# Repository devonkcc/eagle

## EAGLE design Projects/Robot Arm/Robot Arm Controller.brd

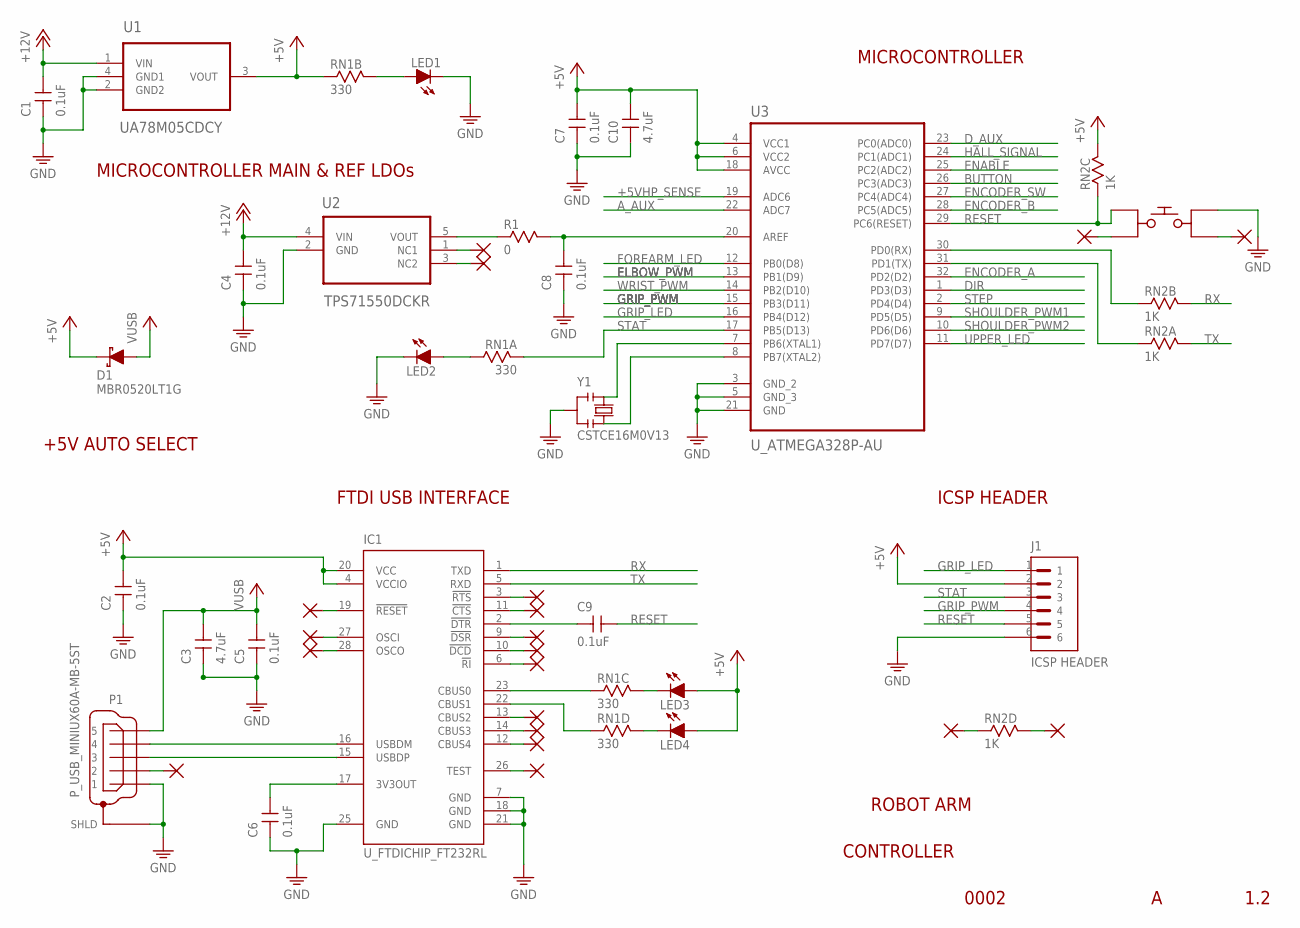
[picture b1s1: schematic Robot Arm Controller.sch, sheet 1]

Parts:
C1, C2, C4, C5, C6, C7, C8, C9: 0.1uF; C0805
C3, C10: 4.7uF; C0805
D1: MBR0520LT1G
IC1: U_FTDICHIP_FT232RL; SSOP28
J1: ICSP HEADER; RECTANGULAR_HEADER_2X3
LED1, LED2, LED3, LED4: D_LEDSML0805; SML0805
P1: P_USB_MINIUX60A-MB-5ST; UX60A-MB-5ST
R1: 0; R0805
RN1: 330; EXBV8V
RN2: 1K; EXBV8V
S1: S_BUTTON_TACTILE_PTS645; PTS645-SMD
U1: UA78M05CDCY; SOT230P700X180-4N
U2: TPS71550DCKR; SOT65P210X110-5N
U3: U_ATMEGA328P-AU; QFP80P900X900X120-32N
Y1: CSTCE16M0V13; CSTCE_V13L

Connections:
+5V: C2.1, C7.1, C10.1, D1.C, IC1.4 (VCCIO), IC1.20 (VCC), J1.2, LED3.A, LED4.A, RN1.2A (1), RN2.3B (2), U1.3 (VOUT), U3.4 (VCC1), U3.6 (VCC2), U3.18 (AVCC); also elsewhere on the board
+5VHP_SENSE: U3.19 (ADC6); also elsewhere on the board
+12V: C1.1, C4.1, U1.1 (VIN), U2.4 (VIN); also elsewhere on the board
A_AUX: U3.22 (ADC7); also elsewhere on the board
BUTTON: U3.26 (PC3(ADC3)); also elsewhere on the board
DIR: U3.1 (PD3(D3)); also elsewhere on the board
D_AUX: U3.23 (PC0(ADC0)); also elsewhere on the board
ELBOW_PWM: U3.13 (PB1(D9)); also elsewhere on the board
ENABLE: U3.25 (PC2(ADC2)); also elsewhere on the board
ENCODER_A: U3.32 (PD2(D2)); also elsewhere on the board
ENCODER_B: U3.28 (PC5(ADC5)); also elsewhere on the board
ENCODER_SW: U3.27 (PC4(ADC4)); also elsewhere on the board
FOREARM_LED: U3.12 (PB0(D8)); also elsewhere on the board
GND: C1.2, C2.2, C3.2, C4.2, C5.2, C6.2, C7.2, C8.2, C10.2, IC1.7 (GND), IC1.18 (GND), IC1.21 (GND), IC1.25 (GND), J1.6, LED1.C, LED2.C, P1.5 (1), P1.M1 (SHLD), P1.M2 (SHLD), P1.M3 (SHLD), P1.M4 (SHLD), S1.1, U1.2 (GND2), U1.4 (GND1), U2.2 (GND), U3.3 (GND_2), U3.5 (GND_3), U3.21 (GND), Y1.2; also elsewhere on the board
GRIP_LED: J1.1, U3.16 (PB4(D12)); also elsewhere on the board
GRIP_PWM: J1.4, U3.15 (PB3(D11)); also elsewhere on the board
HALL_SIGNAL: U3.24 (PC1(ADC1)); also elsewhere on the board
unnamed: LED2.A, RN1.1B (2)
unnamed: U3.8 (PB7(XTAL2)), Y1.3
unnamed: C8.1, R1.2, U3.20 (AREF)
unnamed: IC1.16 (USBDM), P1.2 (4)
unnamed: RN2.1A (1), U3.31 (PD1(TX))
unnamed: C6.1, IC1.17 (3V3OUT)
unnamed: U3.7 (PB6(XTAL1)), Y1.1
unnamed: LED1.A, RN1.2B (2)
unnamed: R1.1, U2.5 (VOUT)
unnamed: RN2.2A (1), U3.30 (PD0(RX))
unnamed: IC1.15 (USBDP), P1.3
unnamed: C9.2, IC1.2 (!DTR)
unnamed: IC1.23 (CBUS0), RN1.3A (1)
unnamed: IC1.22 (CBUS1), RN1.4A (1)
unnamed: LED3.C, RN1.3B (2)
unnamed: LED4.C, RN1.4B (2)
RESET: C9.1, J1.5, RN2.3A (1), S1.3, U3.29 (PC6(RESET))
RX: IC1.1 (TXD), RN2.2B (2)
SHOULDER_PWM1: U3.9 (PD5(D5)); also elsewhere on the board
SHOULDER_PWM2: U3.10 (PD6(D6)); also elsewhere on the board
STAT: J1.3, RN1.1A (1), U3.17 (PB5(D13))
STEP: U3.2 (PD4(D4)); also elsewhere on the board
TX: IC1.5 (RXD), RN2.1B (2)
UPPER_LED: U3.11 (PD7(D7)); also elsewhere on the board
VUSB: C3.1, C5.1, D1.A, P1.1 (5)
WRIST_PWM: U3.14 (PB2(D10)); also elsewhere on the board

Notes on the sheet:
1.2
ROBOT ARM
0002
CONTROLLER
FTDI USB INTERFACE
+5V AUTO SELECT
MICROCONTROLLER MAIN & REF LDOs
MICROCONTROLLER
ICSP HEADER

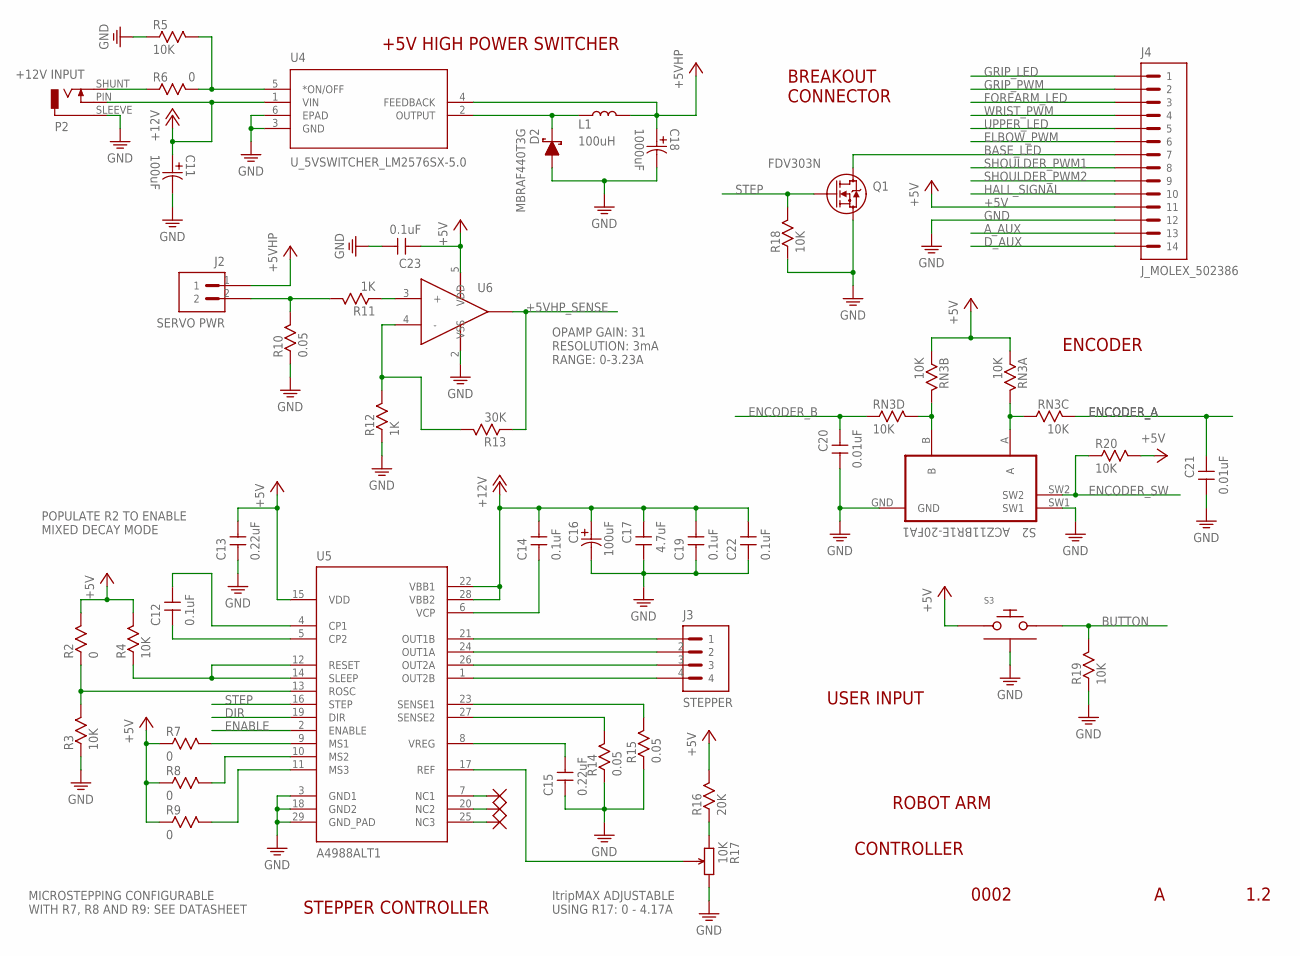
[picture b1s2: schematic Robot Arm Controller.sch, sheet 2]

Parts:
C11, C16: 100uF; NPCAP_PXG_E61
C12, C14, C19, C22, C23: 0.1uF; C0805
C13, C15: 0.22uF; C0805
C17: 4.7uF; C0805
C18: 1000uF; NPCAP_PXG_JA0
C20, C21: 0.01uF; C0805
D2: MBRAF440T3G
J2: SERVO PWR; SREW_TERMINAL_2_POS
J3: STEPPER; SREW_TERMINAL_4_POS
J4: J_MOLEX_502386; MOLEX_502386
L1: 100uH; PA4344.104NLT
P2: +12V INPUT; RASM722PX
Q1: FDV303N; SOT-23-3L
R2, R6, R7, R8, R9: 0; R0805
R3, R4, R5, R18, R19, R20: 10K; R0805
R10, R14, R15: 0.05; R1206
R11, R12: 1K; R0805
R13: 30K; R0805
R16: 20K; R0805
R17: 10K; PANASONIC_P2W_POT
RN3: 10K; EXBV8V
S2: ACZ11BR1E-20FA1; ACZ11BR1E-20FA1-20C
S3: S_BUTTON_TACTILE_KT11S1SA2M35LFG; C&K_SA2M_SA1M
U4: U_5VSWITCHER_LM2576SX-5.0; KTT5_6P22X6P86
U5: A4988ALT1; ALLEGRO_A4988
U6: U_OPAMP_MCP6001T-E/OT; SOT95P270X145-5N

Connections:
+5V: C13.1, C23.2, J4.P11 (11), R2.2, R4.2, R7.1, R8.1, R9.1, R16.2, R20.2, RN3.1A (1), RN3.2A (1), S3.1, U5.15 (VDD), U6.5 (VDD); also elsewhere on the board
+5VHP: C18.+, J2.1, L1.2, U4.4 (FEEDBACK)
+5VHP_SENSE: R13.1, U6.1 (VOUT); also elsewhere on the board
+12V: C11.+, C14.1, C16.+, C17.2, C19.1, C22.1, P2.PIN, U4.1 (VIN), U5.22 (VBB1), U5.28 (VBB2); also elsewhere on the board
A_AUX: J4.P13 (13); also elsewhere on the board
BASE_LED: J4.P7 (7), Q1.S (DRAIN)
BUTTON: R19.2, S3.2; also elsewhere on the board
DIR: U5.19 (DIR); also elsewhere on the board
D_AUX: J4.P14 (14); also elsewhere on the board
ELBOW_PWM: J4.P6 (6); also elsewhere on the board
ENABLE: U5.2 (ENABLE); also elsewhere on the board
ENCODER_A: C21.2, RN3.3A (1); also elsewhere on the board
ENCODER_B: C20.2, RN3.4A (1); also elsewhere on the board
ENCODER_SW: R20.1, S2.SW2; also elsewhere on the board
FOREARM_LED: J4.P3 (3); also elsewhere on the board
GND: C11.-, C13.2, C15.2, C16.-, C17.1, C18.-, C19.2, C20.1, C21.1, C22.2, C23.1, D2.A, J4.P12 (12), P2.SLEEVE, Q1.D (SOURCE), R3.1, R5.1, R10.1, R12.1, R14.1, R15.1, R17.3, R18.1, R19.1, S2.GND, S2.SW1, S3.FRONT (HOUSING), S3.SIDE1 (HOUSING), S3.SIDE2 (HOUSING), U4.3 (GND), U4.6 (EPAD), U5.3 (GND1), U5.18 (GND2), U5.29 (GND_PAD), U6.2 (VSS); also elsewhere on the board
GRIP_LED: J4.P1 (1); also elsewhere on the board
GRIP_PWM: J4.P2 (2); also elsewhere on the board
HALL_SIGNAL: J4.P10 (10); also elsewhere on the board
unnamed: D2.C, L1.1, U4.2 (OUTPUT)
unnamed: RN3.2B (2), RN3.4B (2), S2.B
unnamed: R5.2, R6.2, U4.5 (*ON/OFF)
unnamed: RN3.1B (2), RN3.3B (2), S2.A
unnamed: J3.1, U5.21 (OUT1B)
unnamed: R11.1, U6.3 (+)
unnamed: R12.2, R13.2, U6.4 (-)
unnamed: J2.2, R10.2, R11.2
unnamed: J3.2, U5.24 (OUT1A)
unnamed: J3.3, U5.26 (OUT2A)
unnamed: J3.4, U5.1 (OUT2B)
unnamed: C15.1, U5.8 (VREG)
unnamed: R14.2, U5.27 (SENSE2)
unnamed: R16.1, R17.1
unnamed: R15.2, U5.23 (SENSE1)
unnamed: R17.2, U5.17 (REF)
unnamed: C14.2, U5.6 (VCP)
unnamed: C12.2, U5.5 (CP2)
unnamed: C12.1, U5.4 (CP1)
unnamed: R8.2, U5.10 (MS2)
unnamed: R7.2, U5.9 (MS1)
unnamed: R9.2, U5.11 (MS3)
unnamed: R4.1, U5.12 (RESET), U5.14 (SLEEP)
unnamed: R2.1, R3.2, U5.13 (ROSC)
unnamed: P2.SHUNT, R6.1
SHOULDER_PWM1: J4.P8 (8); also elsewhere on the board
SHOULDER_PWM2: J4.P9 (9); also elsewhere on the board
STEP: Q1.G (GATE), R18.2, U5.16 (STEP); also elsewhere on the board
UPPER_LED: J4.P5 (5); also elsewhere on the board
WRIST_PWM: J4.P4 (4); also elsewhere on the board

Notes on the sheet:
ROBOT ARM
CONTROLLER
0002
1.2
MICROSTEPPING CONFIGURABLE WITH R7, R8 AND R9: SEE DATASHEET
POPULATE R2 TO ENABLE MIXED DECAY MODE
+5V HIGH POWER SWITCHER
STEPPER CONTROLLER
USER INPUT
ENCODER
BREAKOUT CONNECTOR
ItripMAX ADJUSTABLE USING R17: 0 - 4.17A
OPAMP GAIN: 31 RESOLUTION: 3mA RANGE: 0-3.23A

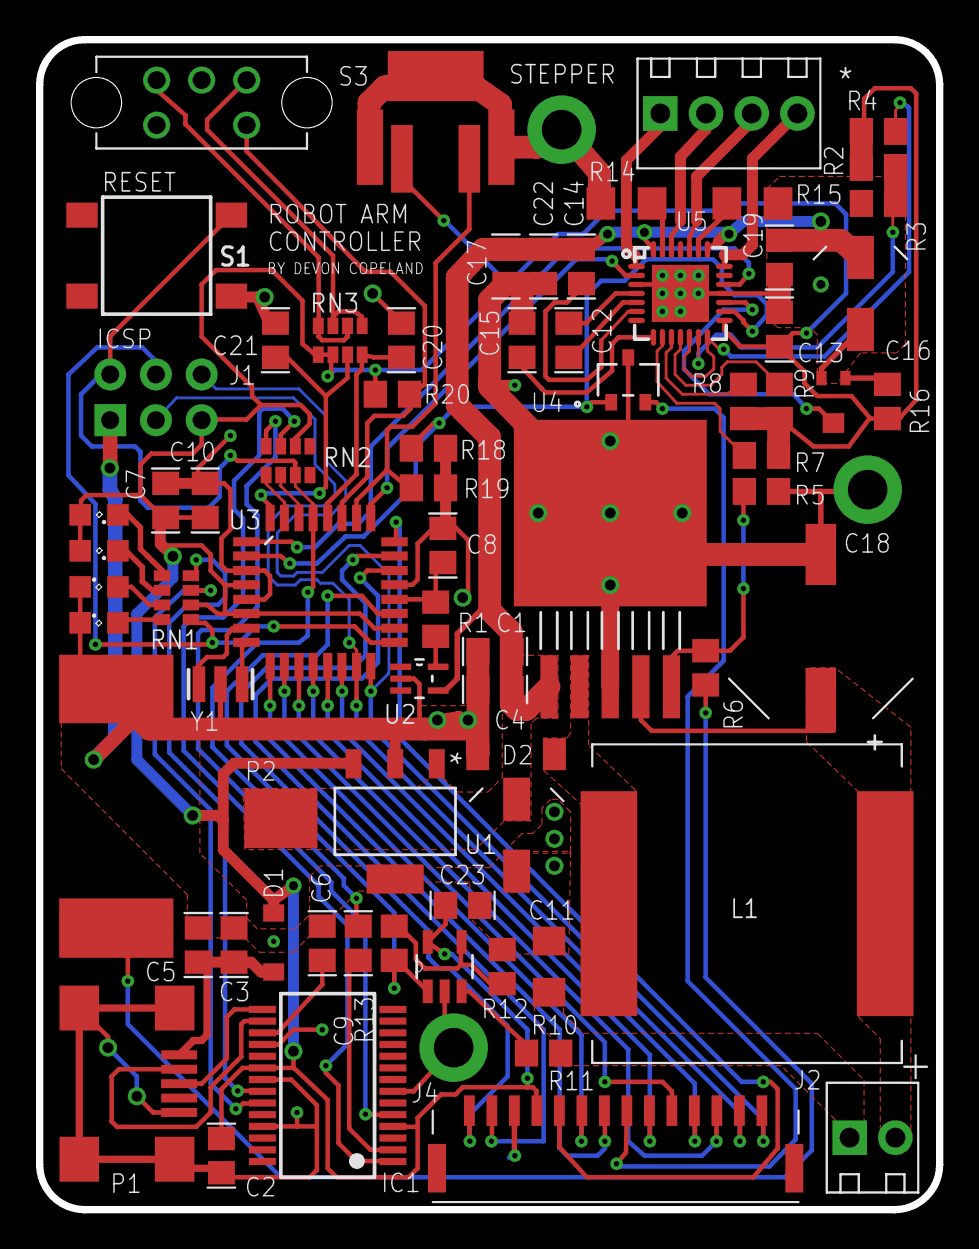
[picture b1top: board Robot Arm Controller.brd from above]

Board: 2 copper layers, 50.0 x 65.0 mm, 71 parts (0 on the bottom side), 70 nets.

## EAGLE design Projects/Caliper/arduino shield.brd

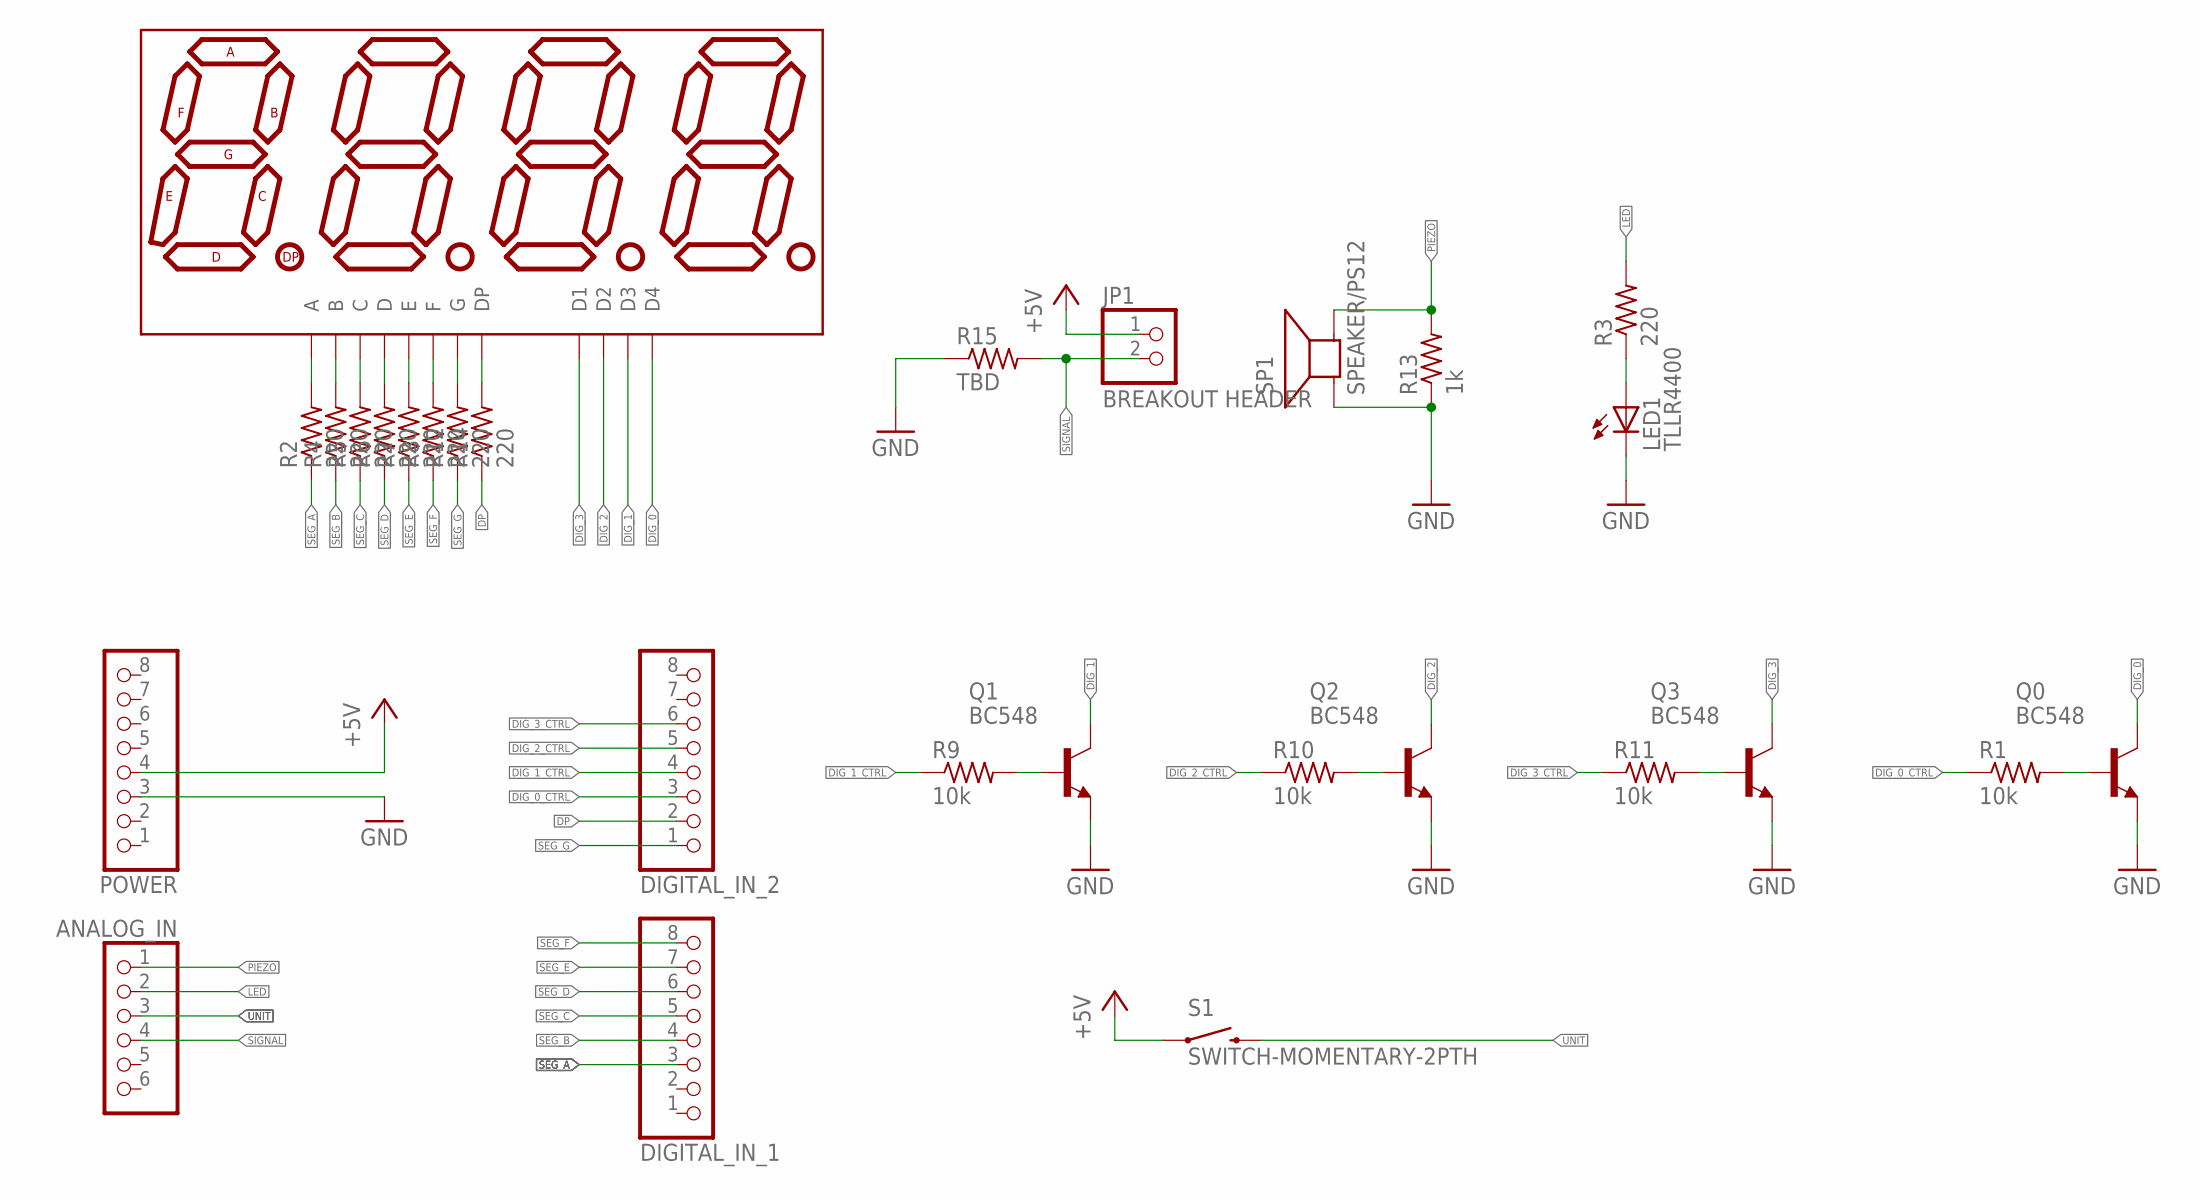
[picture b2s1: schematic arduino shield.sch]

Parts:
ANALOG_IN: PINHD-1X6CB; 1X06-CLEANBIG
DIGITAL_IN_1, DIGITAL_IN_2: PINHD-1X8CLEANBIG; 1X08-CLEANBIG
DISP1: 7-SEGMENT-4DIGIT-COUNTERPTH; 7-SEGMENT-4DIGIT-COUNTER
JP1: BREAKOUT HEADER; 1X02
LED1: TLLR4400; LED3MM
POWER: PINHD-1X8CLEANBIG; 1X08-CLEANBIG
Q0, Q1, Q2, Q3: BC548; TO92-EBC
R1, R9, R10, R11: 10k; 0207/10
R2, R3, R4, R5, R6, R7, R8, R12, R14: 220; 0207/10
R13: 1k; 0207/10
R15: TBD; 0207/10
S1: SWITCH-MOMENTARY-2PTH; TACTILE-PTH
SP1: SPEAKER/PS12; PS12

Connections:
+5V: JP1.1, POWER.4, S1.1
DIG_0: DISP1.6 (D4), Q0.C
DIG_0_CTRL: DIGITAL_IN_2.3, R1.1
DIG_1: DISP1.8 (D3), Q1.C
DIG_1_CTRL: DIGITAL_IN_2.4, R9.1
DIG_2: DISP1.9 (D2), Q2.C
DIG_2_CTRL: DIGITAL_IN_2.5, R10.1
DIG_3: DISP1.12 (D1), Q3.C
DIG_3_CTRL: DIGITAL_IN_2.6, R11.1
DP: DIGITAL_IN_2.2, R14.1
GND: LED1.K (C), POWER.3, Q0.E, Q1.E, Q2.E, Q3.E, R13.1, R15.1, SP1.P$1 (+)
LED: ANALOG_IN.2, R3.2
unnamed: Q0.B, R1.2
unnamed: LED1.A, R3.1
unnamed: DISP1.11 (A), R2.2
unnamed: DISP1.7 (B), R4.2
unnamed: DISP1.4 (C), R5.2
unnamed: DISP1.2 (D), R6.2
unnamed: DISP1.1 (E), R7.2
unnamed: Q1.B, R9.2
unnamed: Q2.B, R10.2
unnamed: Q3.B, R11.2
unnamed: DISP1.10 (F), R8.2
unnamed: DISP1.5 (G), R12.2
unnamed: DISP1.3 (DP), R14.2
PIEZO: ANALOG_IN.1, R13.2, SP1.P$2 (-)
SEG_A: DIGITAL_IN_1.3, R2.1
SEG_B: DIGITAL_IN_1.4, R4.1
SEG_C: DIGITAL_IN_1.5, R5.1
SEG_D: DIGITAL_IN_1.6, R6.1
SEG_E: DIGITAL_IN_1.7, R7.1
SEG_F: DIGITAL_IN_1.8, R8.1
SEG_G: DIGITAL_IN_2.1, R12.1
SIGNAL: ANALOG_IN.4, JP1.2, R15.2
UNIT: ANALOG_IN.3, S1.3 (2)

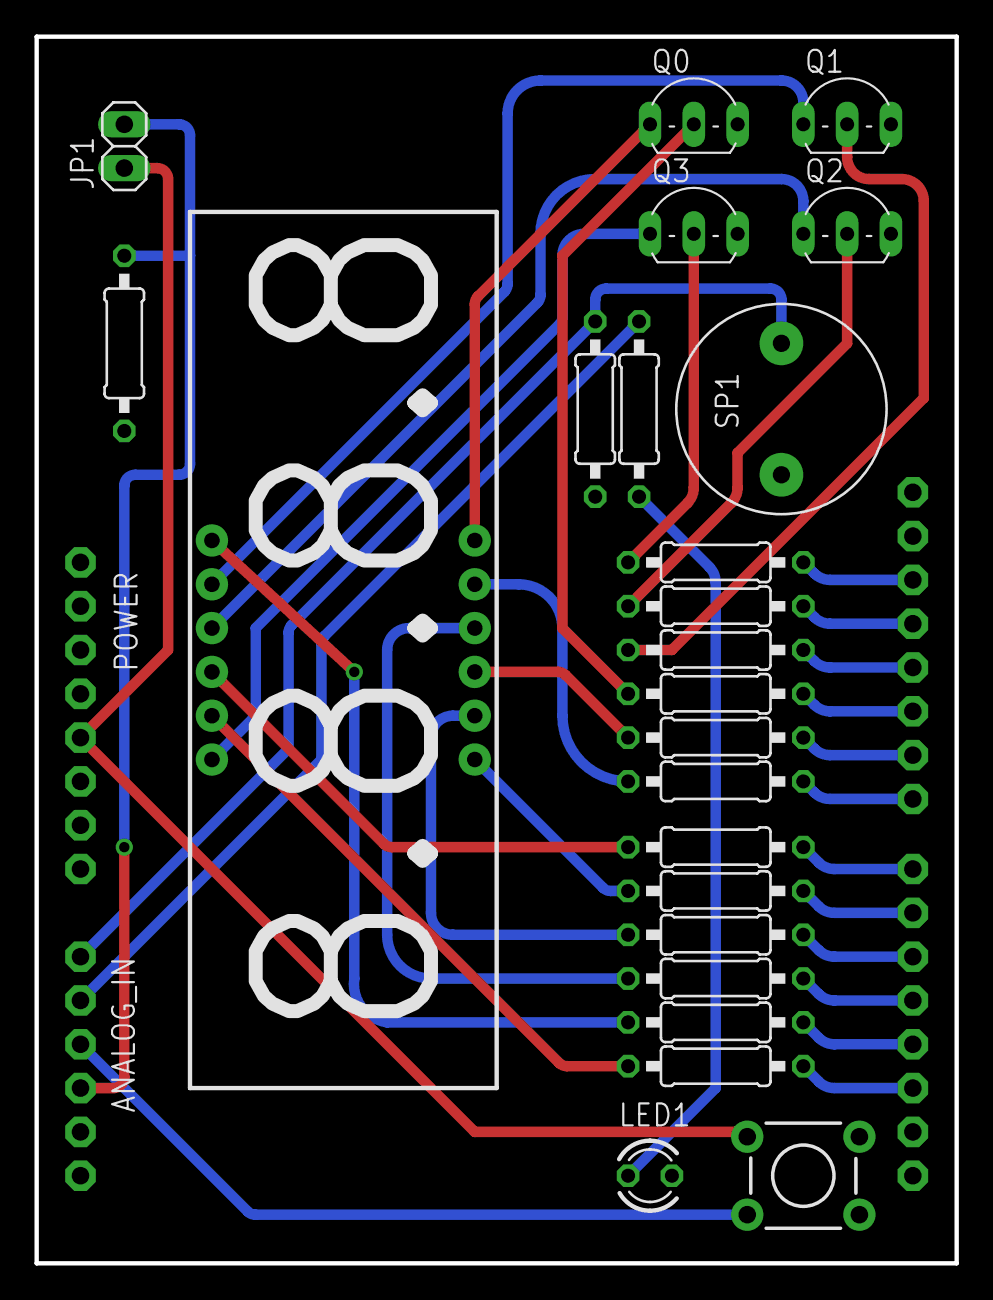
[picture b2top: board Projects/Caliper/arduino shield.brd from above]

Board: 2 copper layers, 53.3 x 71.1 mm, 28 parts (0 on the bottom side), 35 nets.

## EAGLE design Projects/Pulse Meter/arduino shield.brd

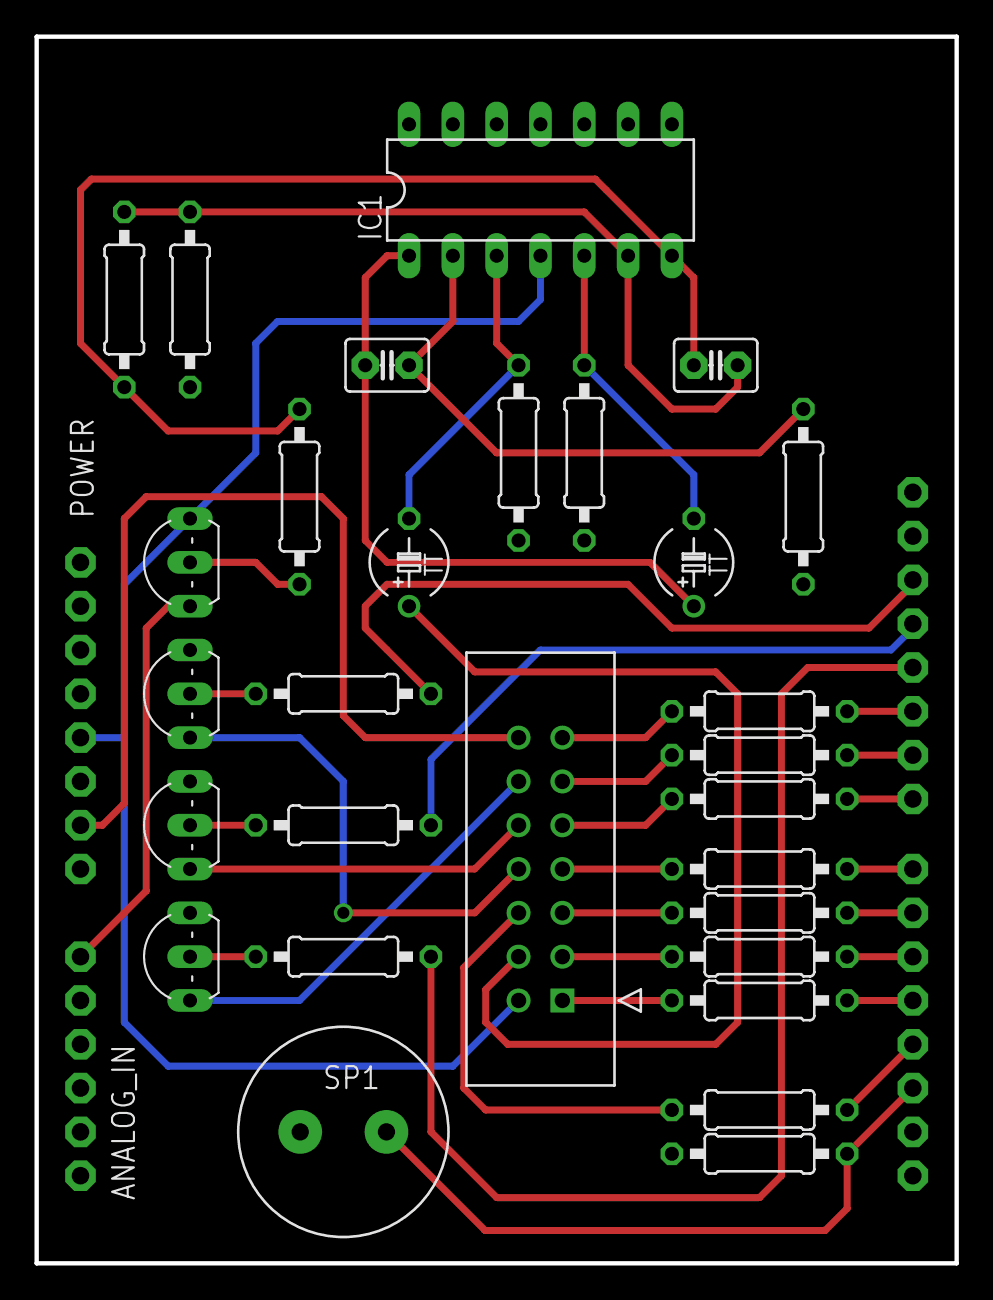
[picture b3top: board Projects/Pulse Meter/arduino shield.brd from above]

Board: 2 copper layers, 53.3 x 71.1 mm, 33 parts (0 on the bottom side), 38 nets.

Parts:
14_PIN_HEADER: 2514-6002UB; 3M_2514-6002UB
ANALOG_IN: 1X06-CLEANBIG
C1, C3: 0.1µF; C2.5-3
C2, C4: 1µF; TAP5-45
DIGITAL_IN_1, DIGITAL_IN_2: 1X08-CLEANBIG
IC1: LM324N; DIL14
POWER: 1X08-CLEANBIG
Q1, Q2, Q3: BC548; TO92-EBC
R1, R2, R3, R4, R5, R6, R7: 430; 0207/10
R8: 220; 0207/10
R9, R10, R11: 10k; 0207/10
R13: 1k; 0207/10
R14, R17: 68K; 0207/10
R15: 8.2K; 0207/10
R16: 470K; 0207/10
R18: 1K; 0207/10
R19: 1.8K; 0207/10
SP1: SPEAKER/PS12; PS12
T1: 2N2222; TO92-EBC-OVAL

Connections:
+5V: 14_PIN_HEADER.2, IC1.4, POWER.4, T1.C
A0: ANALOG_IN.1, T1.E
DIG_1: 14_PIN_HEADER.12, Q1.C
DIG_1_CTRL: DIGITAL_IN_2.4, R9.1
DIG_2: 14_PIN_HEADER.10, Q2.C
DIG_2_CTRL: DIGITAL_IN_2.5, R10.1
DIG_3: 14_PIN_HEADER.8, Q3.C
DIG_3_CTRL: DIGITAL_IN_2.6, R11.1
GND: IC1.11, POWER.3, Q1.E, Q2.E, Q3.E, R13.1, R14.1, R15.1, R17.1, R18.1, SP1.P$1
IR_GND: 14_PIN_HEADER.14, POWER.2
IR_SIGNAL: 14_PIN_HEADER.4, C2.+
unnamed: 14_PIN_HEADER.6, R8.1
unnamed: Q1.B, R9.2
unnamed: Q2.B, R10.2
unnamed: Q3.B, R11.2
unnamed: 14_PIN_HEADER.1, R1.2
unnamed: 14_PIN_HEADER.3, R2.2
unnamed: 14_PIN_HEADER.5, R3.2
unnamed: 14_PIN_HEADER.7, R4.2
unnamed: 14_PIN_HEADER.9, R5.2
unnamed: 14_PIN_HEADER.11, R6.2
unnamed: 14_PIN_HEADER.13, R7.2
unnamed: C2.-, IC1.3, R14.2
unnamed: C1.2, IC1.2, R15.2
unnamed: C1.1, C4.+, IC1.1
unnamed: R19.1, T1.B
unnamed: C4.-, IC1.5, R17.2
unnamed: C3.2, IC1.6, R16.2, R18.2
unnamed: C3.1, IC1.7, R16.1, R19.2
PIEZO: DIGITAL_IN_1.3, R13.2, SP1.P$2
PULSE_LED: DIGITAL_IN_1.4, R8.2
SEG_A: DIGITAL_IN_1.5, R1.1
SEG_B: DIGITAL_IN_1.6, R2.1
SEG_C: DIGITAL_IN_1.7, R3.1
SEG_D: DIGITAL_IN_1.8, R4.1
SEG_E: DIGITAL_IN_2.1, R5.1
SEG_F: DIGITAL_IN_2.2, R6.1
SEG_G: DIGITAL_IN_2.3, R7.1

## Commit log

2016-11-21 Components for robot arm controller
    Added all devices to library for custom controller
    Made Arduino schematic
2016-11-23 Sheet 1 up for review
    Sheet 1 for review
    library refinements
2016-11-23 FTDI, 5VHP, Opamp, Encoder
2016-11-24 Full schematic up for review
2016-11-26 updated robot arm schematic to rev 1.1
    - revisions to library
    - 3A 5V support
    - changed i/o position
    - added component values
2016-11-27 Started placing components
2016-11-27 FTDI and motor controller routed
2016-11-28 Almost done
2016-11-28 everything done except ground planes
2016-11-29 All routing and positioning done
2016-11-29 Entire board up for review
2016-11-30 Design Review 1, Solved all DRC errors
2016-12-03 gerber files

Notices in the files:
parts and their libraries:
SparkFun-Electromechanical: Licensing: Creative Commons ShareAlike 4.0 International - https://creativecommons.org/licenses/by-sa/4.0
COPYRIGHT: Copyright C 2015 Accelerated Designs. All rights reserved
